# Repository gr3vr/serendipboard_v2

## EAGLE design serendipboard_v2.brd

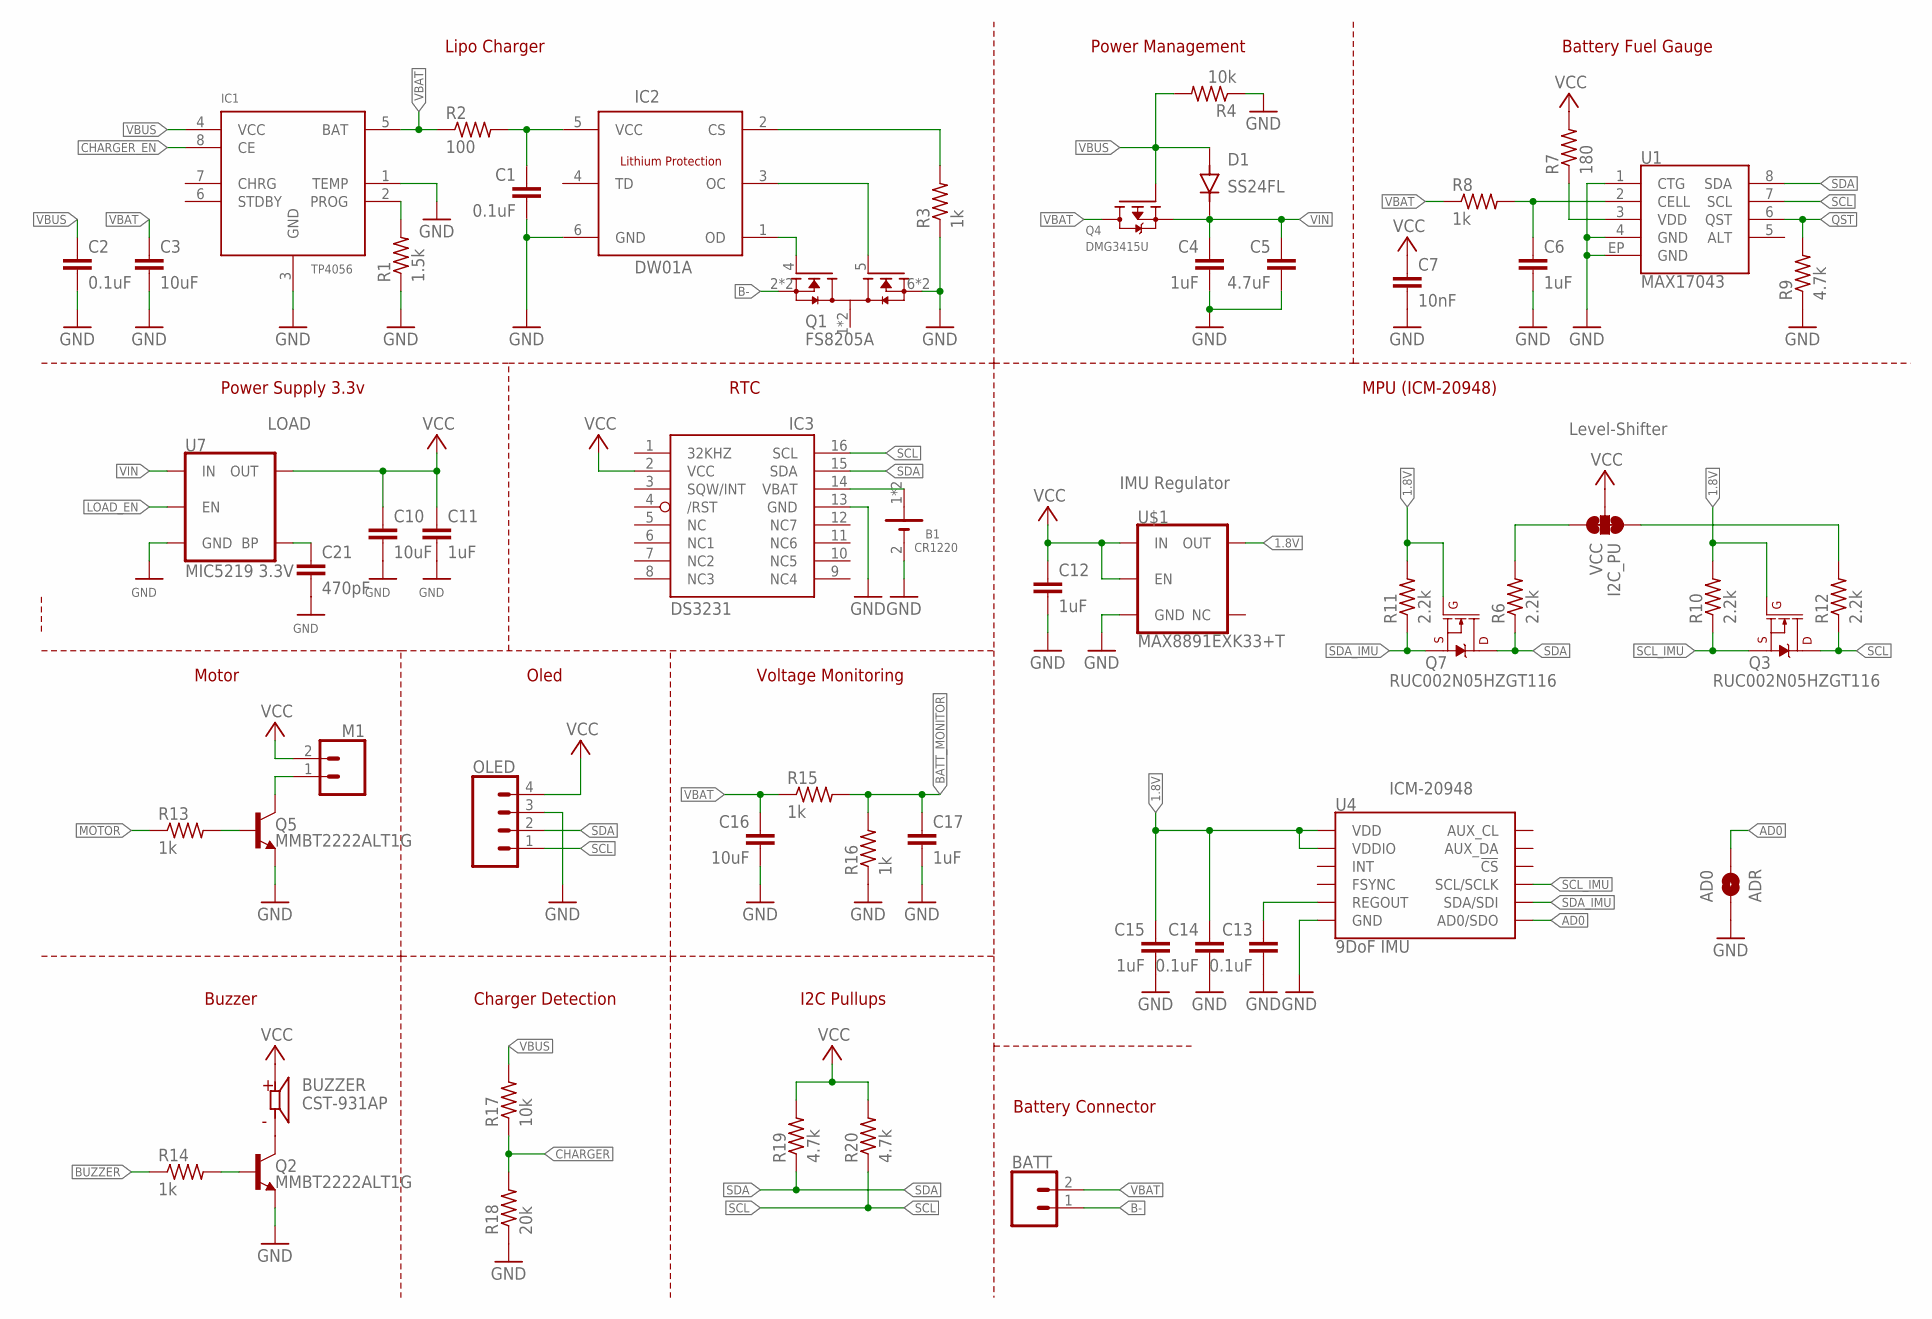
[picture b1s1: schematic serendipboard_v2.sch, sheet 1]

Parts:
AD0: ADR; SMT-JUMPER_2_NO_NO-SILK
B1: CR1220; BAT_3000TR
BATT: CONN_02; 1X02
BUZZER: CST-931AP; CUI_CST-931AP
C1, C2, C13, C14: 0.1uF; C0402
C3, C10, C16: 10uF; C0402
C4, C6, C11, C12, C15, C17: 1uF; C0402
C5: 4.7uF; C0402
C7: 10nF; C0402
C21: 470pF; C0402
D1: SS24FL; SODFL3617X108N
IC1: TP4056; SOP-8
IC2: DW01A; SOT23-6
IC3: DS3231/SO; SO16W
M1: CONN_02; 1X02
OLED: CONN_04PTH; 1X04
Q1: FS8205A; SOP65P640X120-8N
Q2, Q5: MMBT2222ALT1G; SOT23-3
Q3, Q7: RUC002N05HZGT116; SOT23-3
Q4: DMG3415U; SOT23-R
R1: 1.5k; R0402
R2: 100; R0402
R3, R8, R13, R14, R15, R16: 1k; R0402
R4, R17: 10k; R0402
R6, R10, R11, R12: 2.2k; R0402
R7: 180; R0402
R9, R19, R20: 4.7k; R0402
R18: 20k; R0402
U1: MAX17043; TDFN-8
U4: 9DoF IMU; QFN24-3X3-ICM-20948
U7: MIC5219 3.3V; SOT23-5
U$1: MAX8891EXK33+T; SC70
VCC: I2C_PU; SMT-JUMPER_3_2-NC_TRACE_NO-SILK

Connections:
1.8V: C14.1, C15.1, Q3.1 (G), Q7.1 (G), R10.2, R11.2, U4.8 (VDDIO), U4.13 (VDD), U$1.5 (OUT)
AD0: AD0.2, U4.9 (AD0/SDO)
B-: BATT.1, Q1.2 (S1), Q1.3 (S1)
BATT_MONITOR: C17.1, R15.2, R16.2; also elsewhere on the board
BUZZER: R14.1; also elsewhere on the board
CHARGER: R17.1, R18.2; also elsewhere on the board
CHARGER_EN: IC1.8 (CE); also elsewhere on the board
GND: AD0.1, B1.2 (-), C1.2, C2.2, C3.2, C4.2, C5.2, C6.2, C7.2, C10.2, C11.2, C12.2, C13.2, C14.2, C15.2, C16.2, C17.2, C21.2, IC1.1 (TEMP), IC1.3 (GND), IC2.6 (GND), IC3.13 (GND), OLED.3, Q1.6 (S2), Q1.7 (S2), Q2.2 (E), Q5.2 (E), R1.1, R3.1, R4.1, R9.1, R16.1, R18.1, U1.1 (CTG), U1.4 (GND), U1.EP (GND), U4.18 (GND), U4.20 (GND), U7.2 (GND), U$1.2 (GND); also elsewhere on the board
LOAD_EN: U7.3 (EN); also elsewhere on the board
MOTOR: R13.1; also elsewhere on the board
unnamed: IC1.2 (PROG), R1.2
unnamed: IC2.3 (OC), Q1.5 (G2)
unnamed: C1.1, IC2.5 (VCC), R2.2
unnamed: IC2.1 (OD), Q1.4 (G1)
unnamed: IC2.2 (CS), R3.2
unnamed: R7.1, U1.3 (VDD)
unnamed: C6.1, R8.2, U1.2 (CELL)
unnamed: B1.1 (+), B1.3 (+), IC3.14 (VBAT)
unnamed: R6.2, VCC.3
unnamed: C13.1, U4.10 (REGOUT)
unnamed: R12.2, VCC.1
unnamed: Q5.1 (B), R13.2
unnamed: Q2.1 (B), R14.2
unnamed: M1.1, Q5.3 (C)
unnamed: BUZZER.M, Q2.3 (C)
unnamed: C21.1, U7.4 (BP)
QST: R9.2, U1.6 (QST); also elsewhere on the board
SCL: IC3.16 (SCL), OLED.1, Q3.3 (D), R12.1, R20.1, U1.7 (SCL); also elsewhere on the board
SCL_IMU: Q3.2 (S), R10.1, U4.23 (SCL/SCLK)
SDA: IC3.15 (SDA), OLED.2, Q7.3 (D), R6.1, R19.1, U1.8 (SDA); also elsewhere on the board
SDA_IMU: Q7.2 (S), R11.1, U4.24 (SDA/SDI)
VBAT: BATT.2, C3.1, C16.1, IC1.5 (BAT), Q4.3 (D), R2.1, R8.1, R15.1
VBUS: C2.1, D1.A, IC1.4 (VCC), Q4.1 (G), R4.2, R17.2; also elsewhere on the board
VCC: BUZZER.P, C7.1, C10.1, C11.1, C12.1, IC3.2 (VCC), M1.2, OLED.4, R7.2, R19.2, R20.2, U7.5 (OUT), U$1.1 (IN), U$1.3 (EN), VCC.2
VIN: C4.1, C5.1, D1.C, Q4.2 (S), U7.1 (IN); also elsewhere on the board

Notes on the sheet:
Lipo Charger
Power Management
Battery Fuel Gauge
Power Supply 3.3v
LOAD
RTC
IMU Regulator
MPU (ICM-20948)
Level-Shifter
ICM-20948
Battery Connector
Motor
Voltage Monitoring
Buzzer
Charger Detection
I2C Pullups
Oled

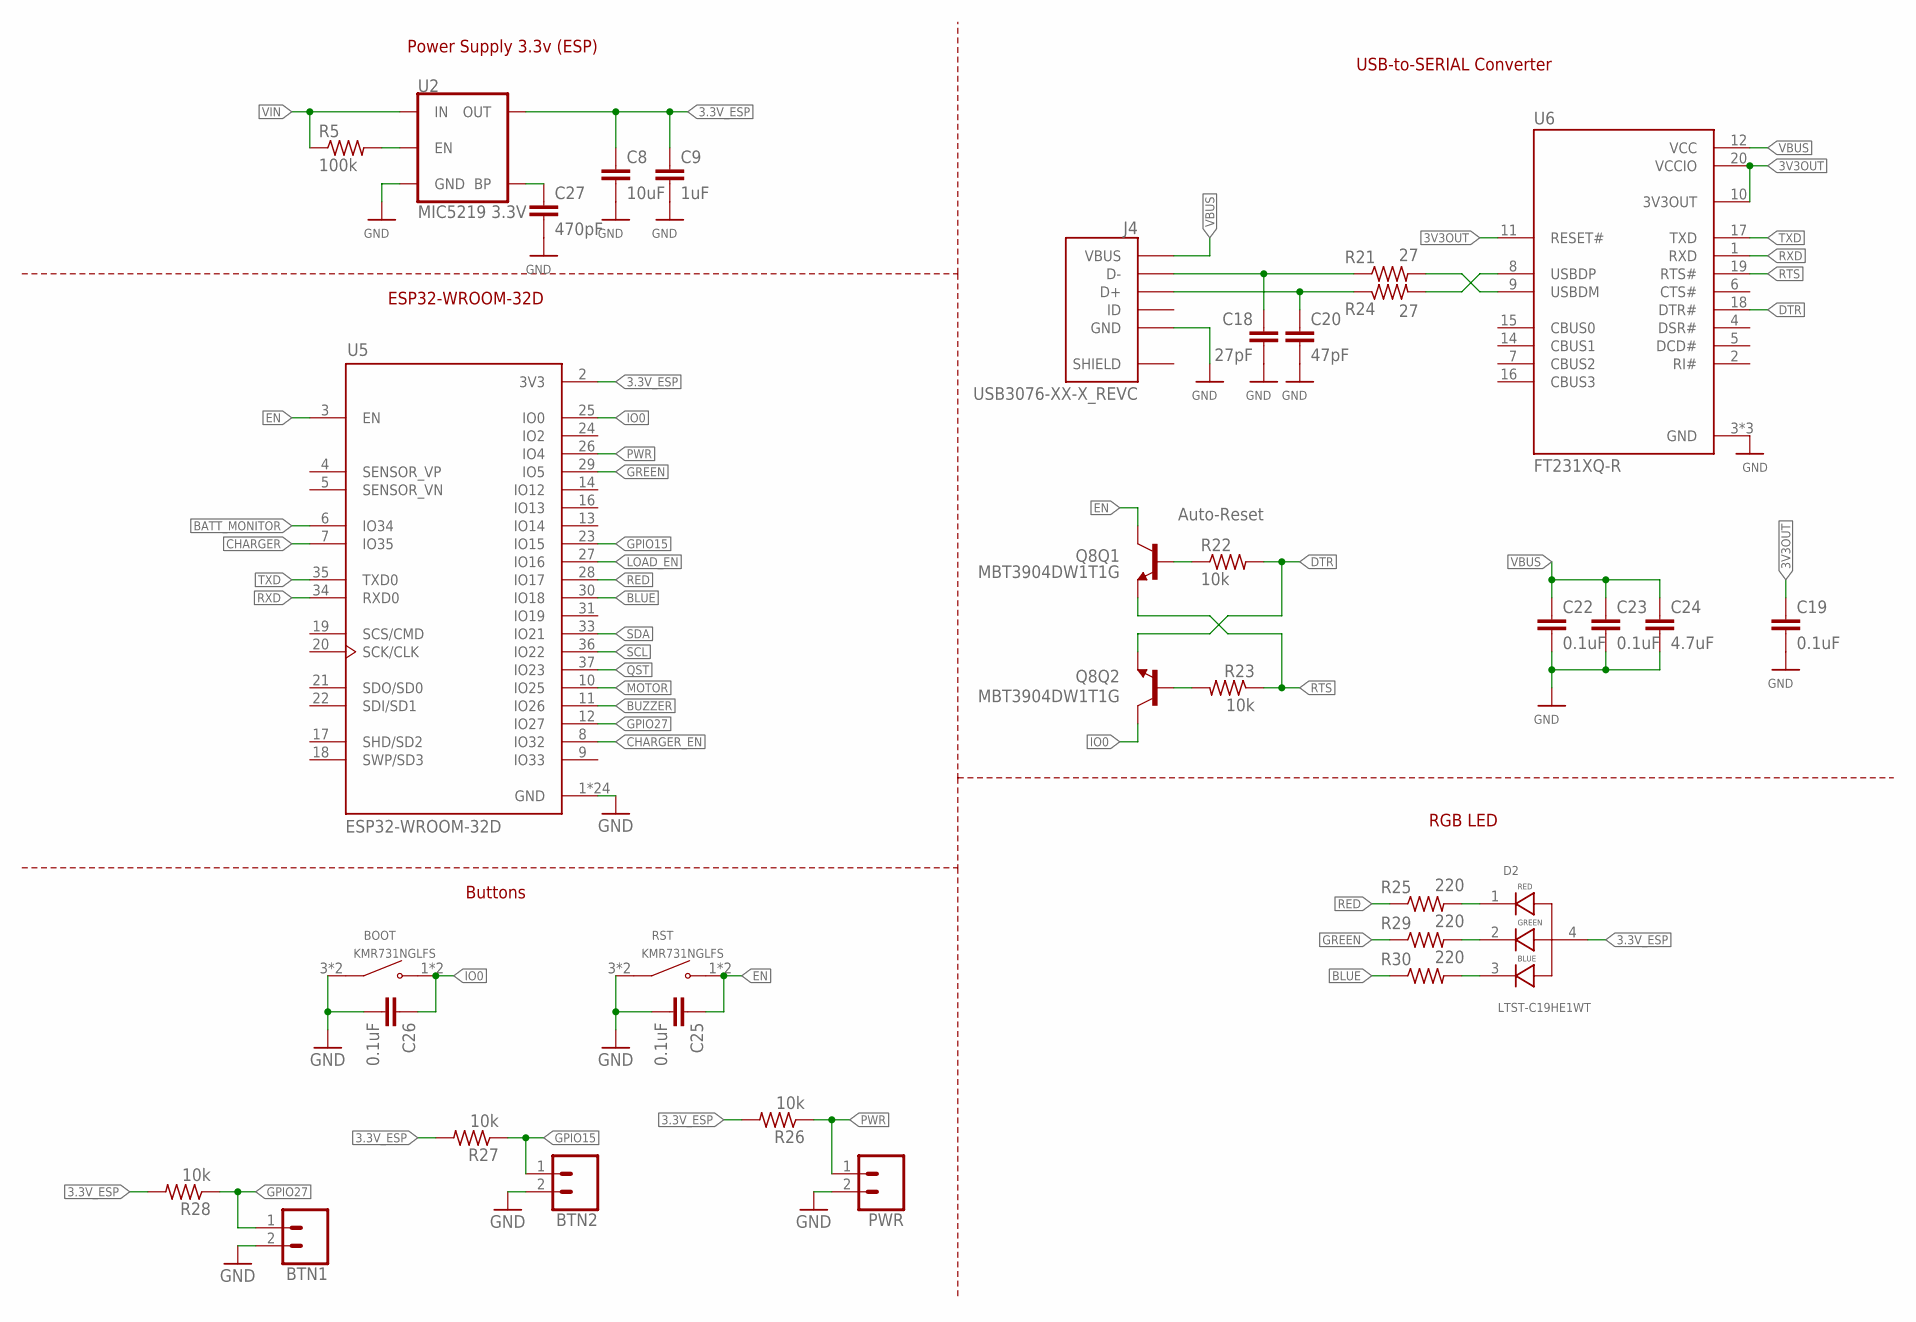
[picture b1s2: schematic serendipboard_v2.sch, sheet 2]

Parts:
BOOT: KMR731NGLFS; SW_KMR731NGLFS
BTN1, BTN2: CONN_02; 1X02
C8: 10uF; C0402
C9: 1uF; C0402
C18: 27pF; C0402
C19, C22, C23, C25, C26: 0.1uF; C0402
C20: 47pF; C0402
C24: 4.7uF; C0402
C27: 470pF; C0402
D2: LTST-C19HE1WT; LED_LTST-C19HE1WT
J4: USB3076-XX-X_REVC; GCT_USB3076-XX-X_REVC
PWR: CONN_02; 1X02
Q8: MBT3904DW1T1G; SC70-6
R5: 100k; R0402
R21, R24: 27; R0402
R22, R23, R26, R27, R28: 10k; R0402
R25, R29, R30: 220; R0402
RST: KMR731NGLFS; SW_KMR731NGLFS
U2: MIC5219 3.3V; SOT23-5
U5: ESP32-WROOM-32D; MODULE_ESP32-WROOM-32D
U6: FT231XQ-R; QFN50P400X400X80-21N

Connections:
3.3V_ESP: C8.1, C9.1, D2.4, R26.2, R27.2, R28.2, U2.5 (OUT), U5.2 (3V3)
3V3OUT: C19.1, U6.10 (3V3OUT), U6.11 (RESET#), U6.20 (VCCIO)
BATT_MONITOR: U5.6 (IO34); also elsewhere on the board
BLUE: R30.1, U5.30 (IO18)
BUZZER: U5.11 (IO26); also elsewhere on the board
CHARGER: U5.7 (IO35); also elsewhere on the board
CHARGER_EN: U5.8 (IO32); also elsewhere on the board
DTR: Q8.1 (E), R22.2, U6.18 (DTR#)
EN: C25.1, Q8.3 (C), RST.1 (NO), RST.2 (NO), U5.3 (EN)
GND: BOOT.3 (COM), BOOT.4 (COM), BTN1.2, BTN2.2, C8.2, C9.2, C18.2, C19.2, C20.2, C22.2, C23.2, C24.2, C25.2, C26.2, C27.2, J4.5 (GND), PWR.2, RST.3 (COM), RST.4 (COM), U2.2 (GND), U5.1 (GND), U5.15 (GND), U5.38 (GND), U5.39_1 (GND), U5.39_2 (GND), U5.39_3 (GND), U5.39_4 (GND), U5.39_5 (GND), U5.39_6 (GND), U5.39_7 (GND), U5.39_8 (GND), U5.39_9 (GND), U5.39_10 (GND), U5.39_11 (GND), U5.39_12 (GND), U5.39_13 (GND), U5.39_14 (GND), U5.39_15 (GND), U5.39_16 (GND), U5.39_17 (GND), U5.39_18 (GND), U5.39_19 (GND), U5.39_20 (GND), U5.39_21 (GND), U6.3 (GND), U6.13 (GND), U6.21 (GND); also elsewhere on the board
GPIO15: BTN2.1, R27.1, U5.23 (IO15)
GPIO27: BTN1.1, R28.1, U5.12 (IO27)
GREEN: R29.1, U5.29 (IO5)
IO0: BOOT.1 (NO), BOOT.2 (NO), C26.1, Q8.6 (C), U5.25 (IO0)
LOAD_EN: U5.27 (IO16); also elsewhere on the board
MOTOR: U5.10 (IO25); also elsewhere on the board
unnamed: C27.1, U2.4 (BP)
unnamed: Q8.5 (B), R22.1
unnamed: C18.1, J4.2 (D-), R21.1
unnamed: Q8.2 (B), R23.2
unnamed: R21.2, U6.9 (USBDM)
unnamed: C20.1, J4.3 (D+), R24.1
unnamed: R24.2, U6.8 (USBDP)
unnamed: R5.2, U2.3 (EN)
unnamed: D2.1, R25.2
unnamed: D2.2, R29.2
unnamed: D2.3, R30.2
PWR: PWR.1, R26.1, U5.26 (IO4)
QST: U5.37 (IO23); also elsewhere on the board
RED: R25.1, U5.28 (IO17)
RTS: Q8.4 (E), R23.1, U6.19 (RTS#)
RXD: U5.34 (RXD0), U6.1 (RXD)
SCL: U5.36 (IO22); also elsewhere on the board
SDA: U5.33 (IO21); also elsewhere on the board
SHIELD: J4.6 (SHIELD), J4.7 (SHIELD), J4.8 (SHIELD), J4.9 (SHIELD), J4.10 (SHIELD), J4.11 (SHIELD)
TXD: U5.35 (TXD0), U6.17 (TXD)
VBUS: C22.1, C23.1, C24.1, J4.1 (VBUS), U6.12 (VCC); also elsewhere on the board
VIN: R5.1, U2.1 (IN); also elsewhere on the board

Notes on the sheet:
Power Supply 3.3v (ESP)
USB-to-SERIAL Converter
Buttons
ESP32-WROOM-32D
Auto-Reset
RGB LED

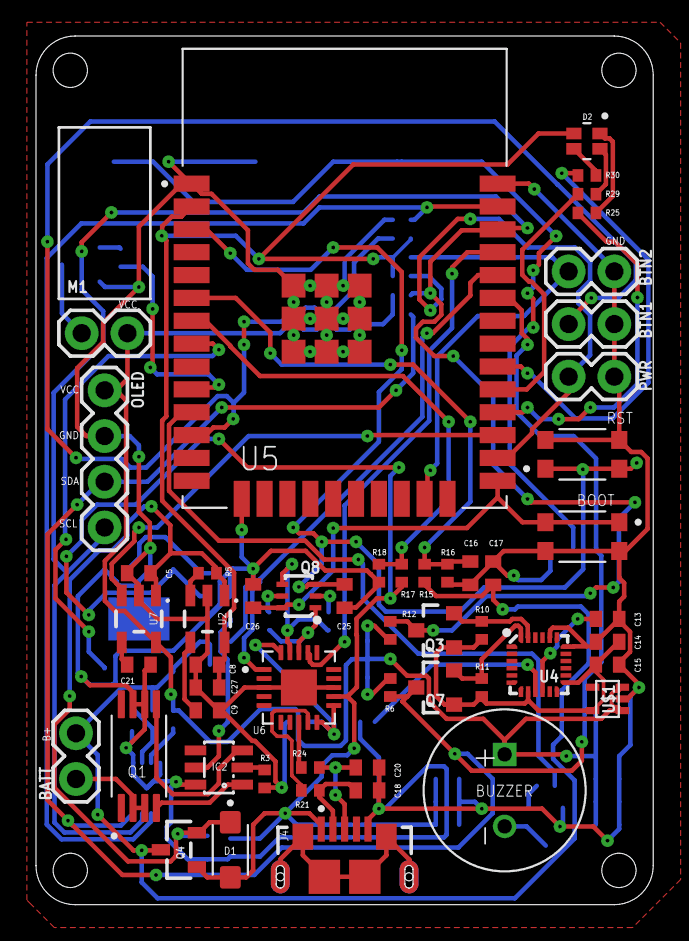
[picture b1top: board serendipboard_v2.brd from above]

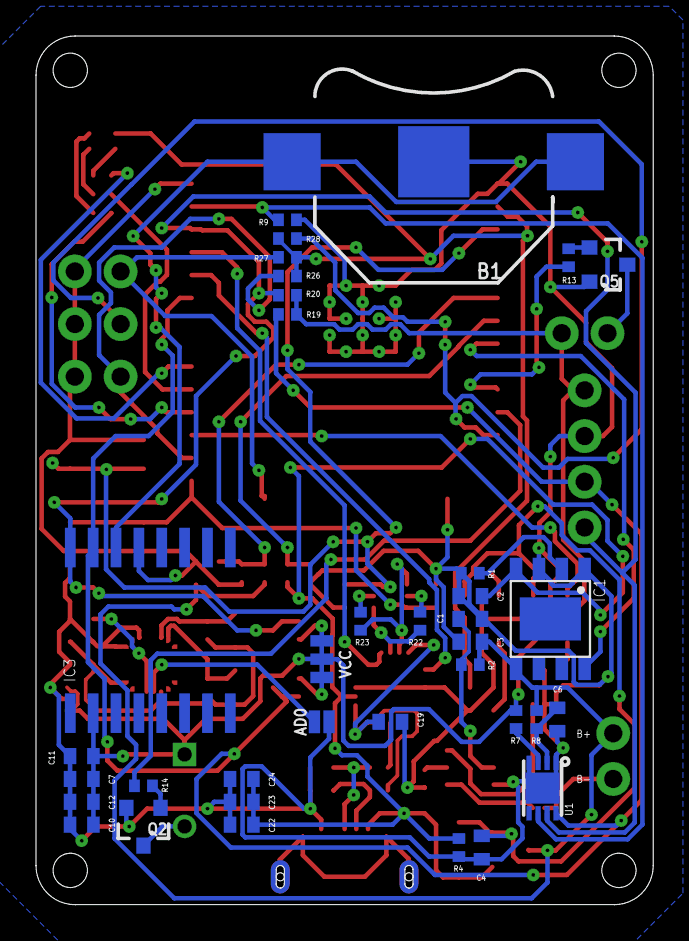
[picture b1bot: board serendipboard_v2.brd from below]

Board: 2 copper layers, 34.3 x 48.3 mm, 89 parts (36 on the bottom side), 61 nets.

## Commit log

2021-03-24 DRC Checked

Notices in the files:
parts and their libraries:
microbuilder: This work is placed in the public domain, and may be freely used for commercial and non-commercial work with the following conditions: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
SparkFun-Connectors: Licensing: Creative Commons ShareAlike 4.0 International - https://creativecommons.org/licenses/by-sa/4.0
